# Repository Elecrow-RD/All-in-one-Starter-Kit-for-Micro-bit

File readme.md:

### 1, Product picture

https://www.elecrow.com/all-in-one-starter-kit-for-micro-bit-common-board-design-rich-modules-and-lessons.html

### 2, Product version number

|      | Hardware | Software | Remark |
| ---- | -------- | -------- | ------ |
| 1    | V1.0     | V1.0     | latest |

### 3, product information

- Main Processor IC: micro:bit
- Interface: Type-C Interface
- Size: 195\*170*46(mm)
- Material:PP(Non-toxic)
- Weight: 380g

|                         | [All-in-one Starter Kit for Micro:bit](https://www.elecrow.com/all-in-one-starter-kit-for-micro-bit-common-board-design-rich-modules-and-lessons.html) |
| ----------------------- | ------------------------------------------------------------ |
| Main Processor          | micro:bit                                                    |
| Number of Sensors       | 13 sensors                                                   |
| Sensor Board Design     | Integrated sensor board, no soldering or complex wiring required |
| Programming Environment | Based on micro:bit visual modular programming                |
| Number of Tutorials     | 21 creative tutorials                                        |
| Dimension               | 195x170x46mm                                                 |
| Target Audience         | Students, teachers, hardware enthusiasts                     |
| Application Scenarios   | Ideal for learning micro:bit programming basics              |

### 4,Quick Start

#### Go to the Micro:bit website:https://makecode.microbit.org/

#### Enter the online editor

### 5,Folder structure.

|--3D file： Contains 3D model files (.stp) for the hardware. These files can be used for visualization, enclosure design, or integration into CAD software.

|--Eagle_SCH&PCB: Contains **Eagle CAD** schematic (`.sch`) and PCB layout (`.brd`) files. These are used for circuit design and PCB manufacturing.

|--example: Provides example code and projects to demonstrate how to use the hardware and libraries. These examples help users get started quickly.

### 6,Pin definition

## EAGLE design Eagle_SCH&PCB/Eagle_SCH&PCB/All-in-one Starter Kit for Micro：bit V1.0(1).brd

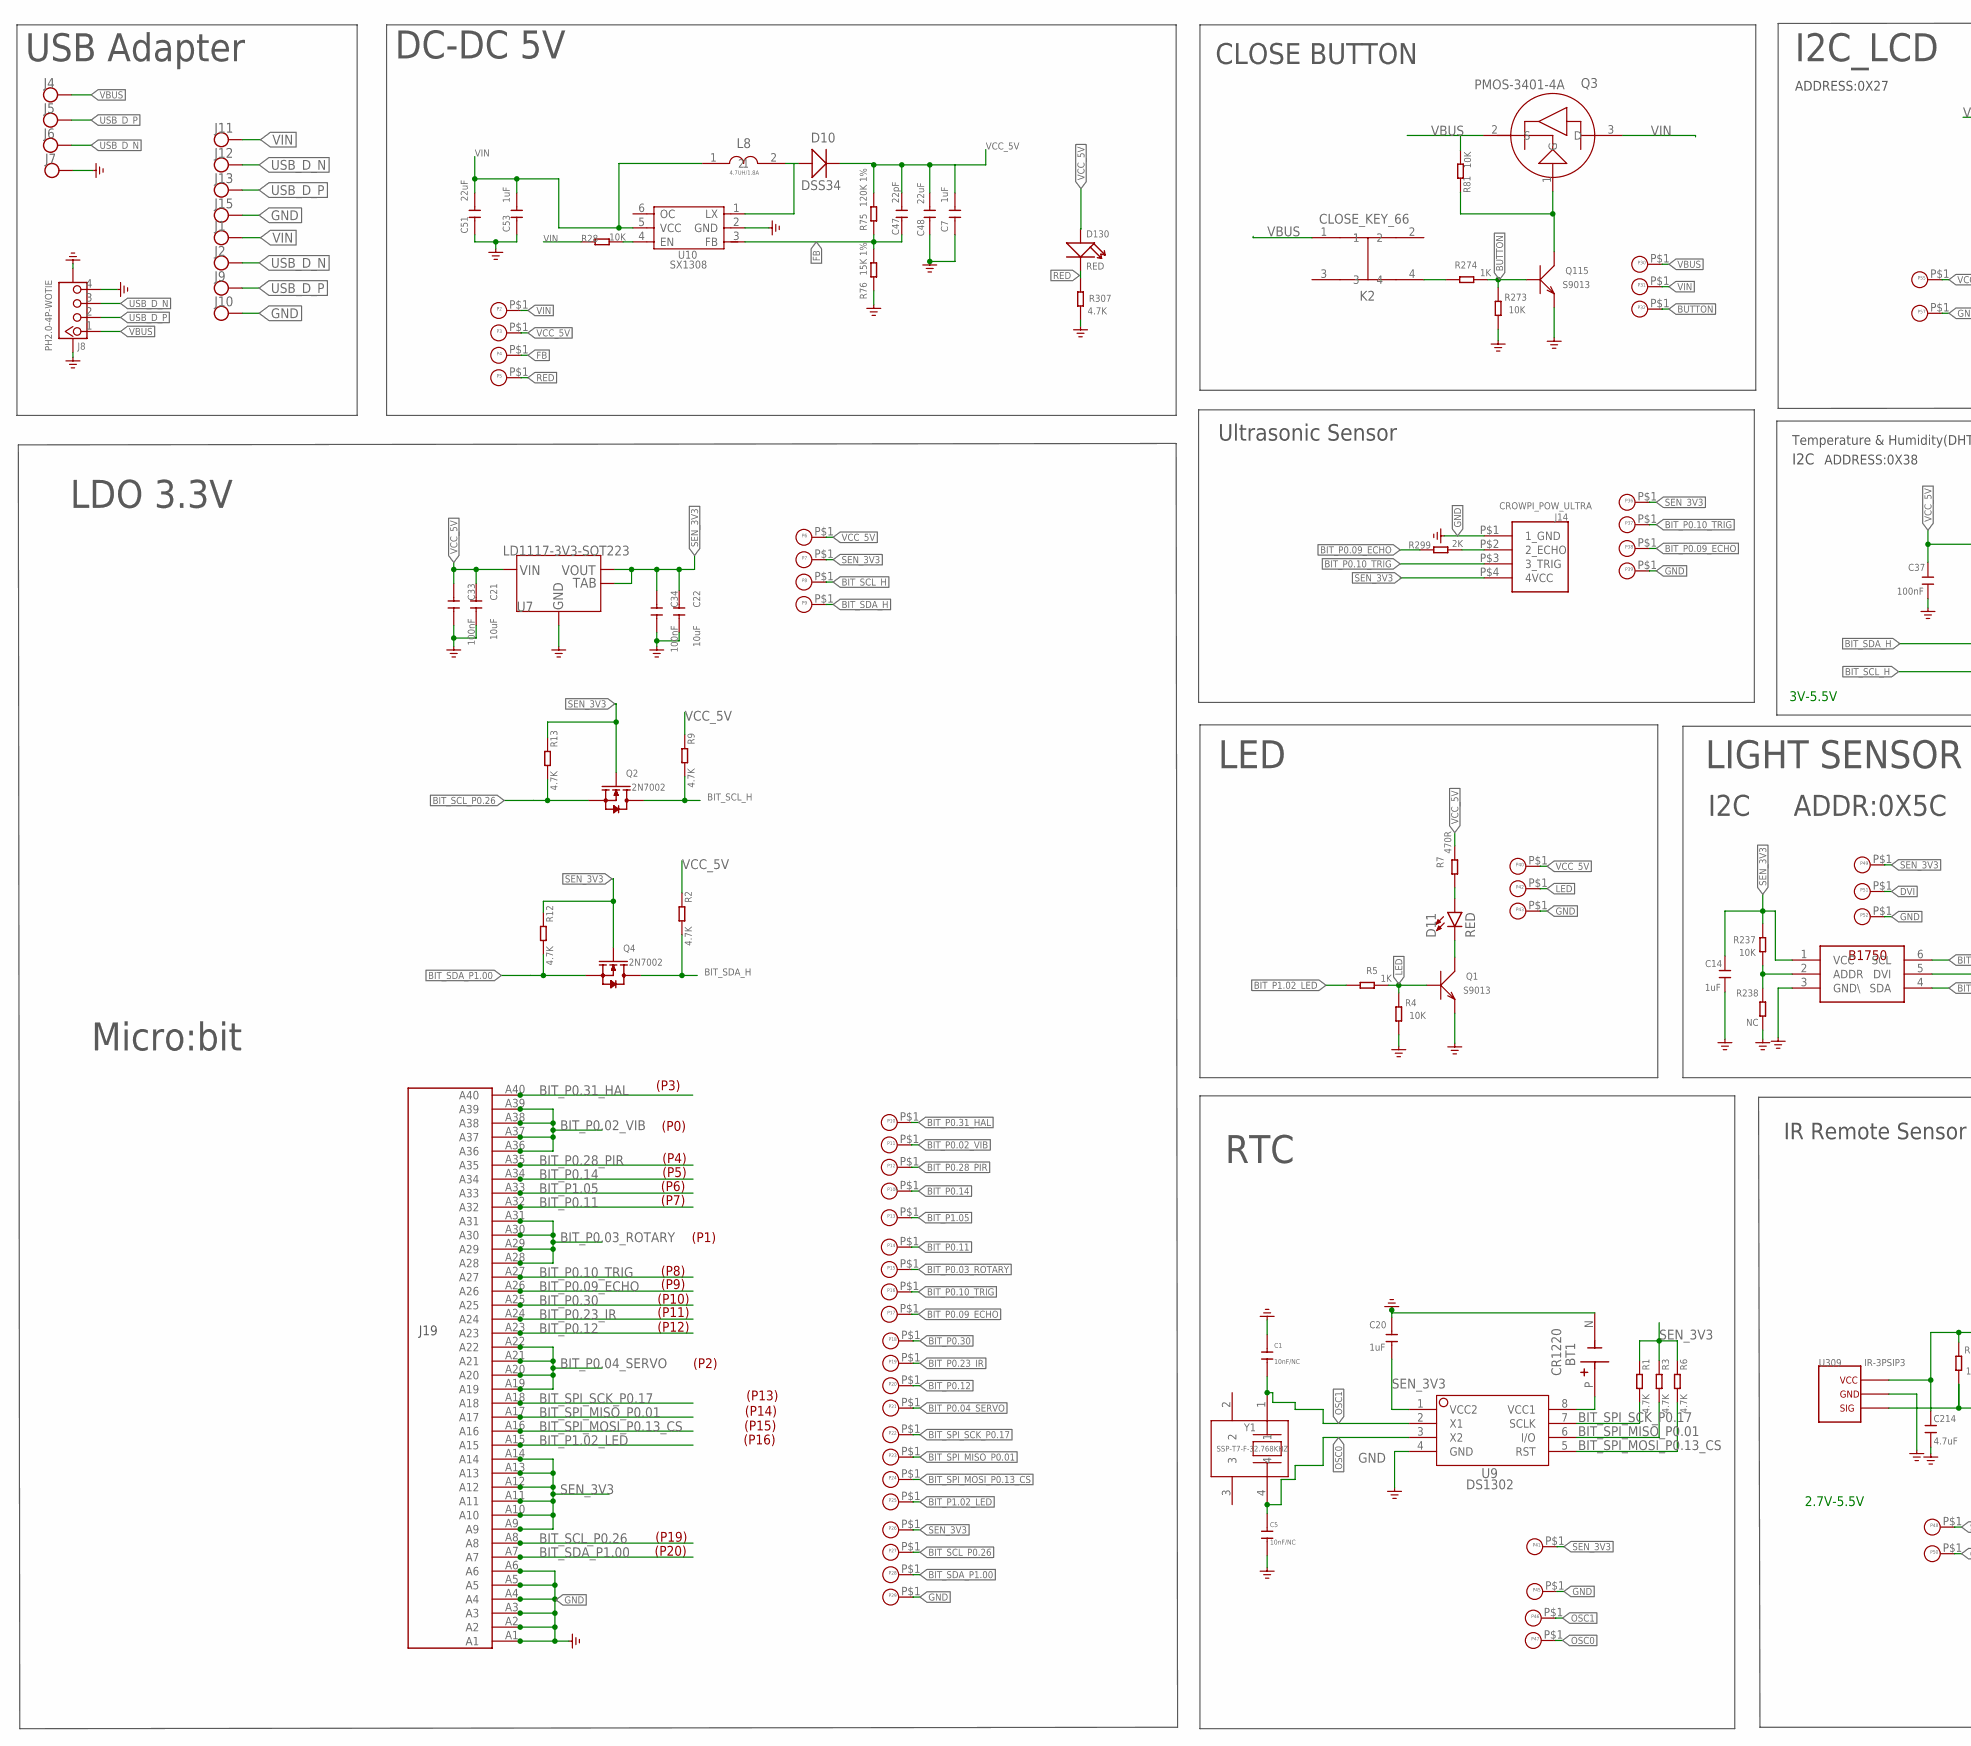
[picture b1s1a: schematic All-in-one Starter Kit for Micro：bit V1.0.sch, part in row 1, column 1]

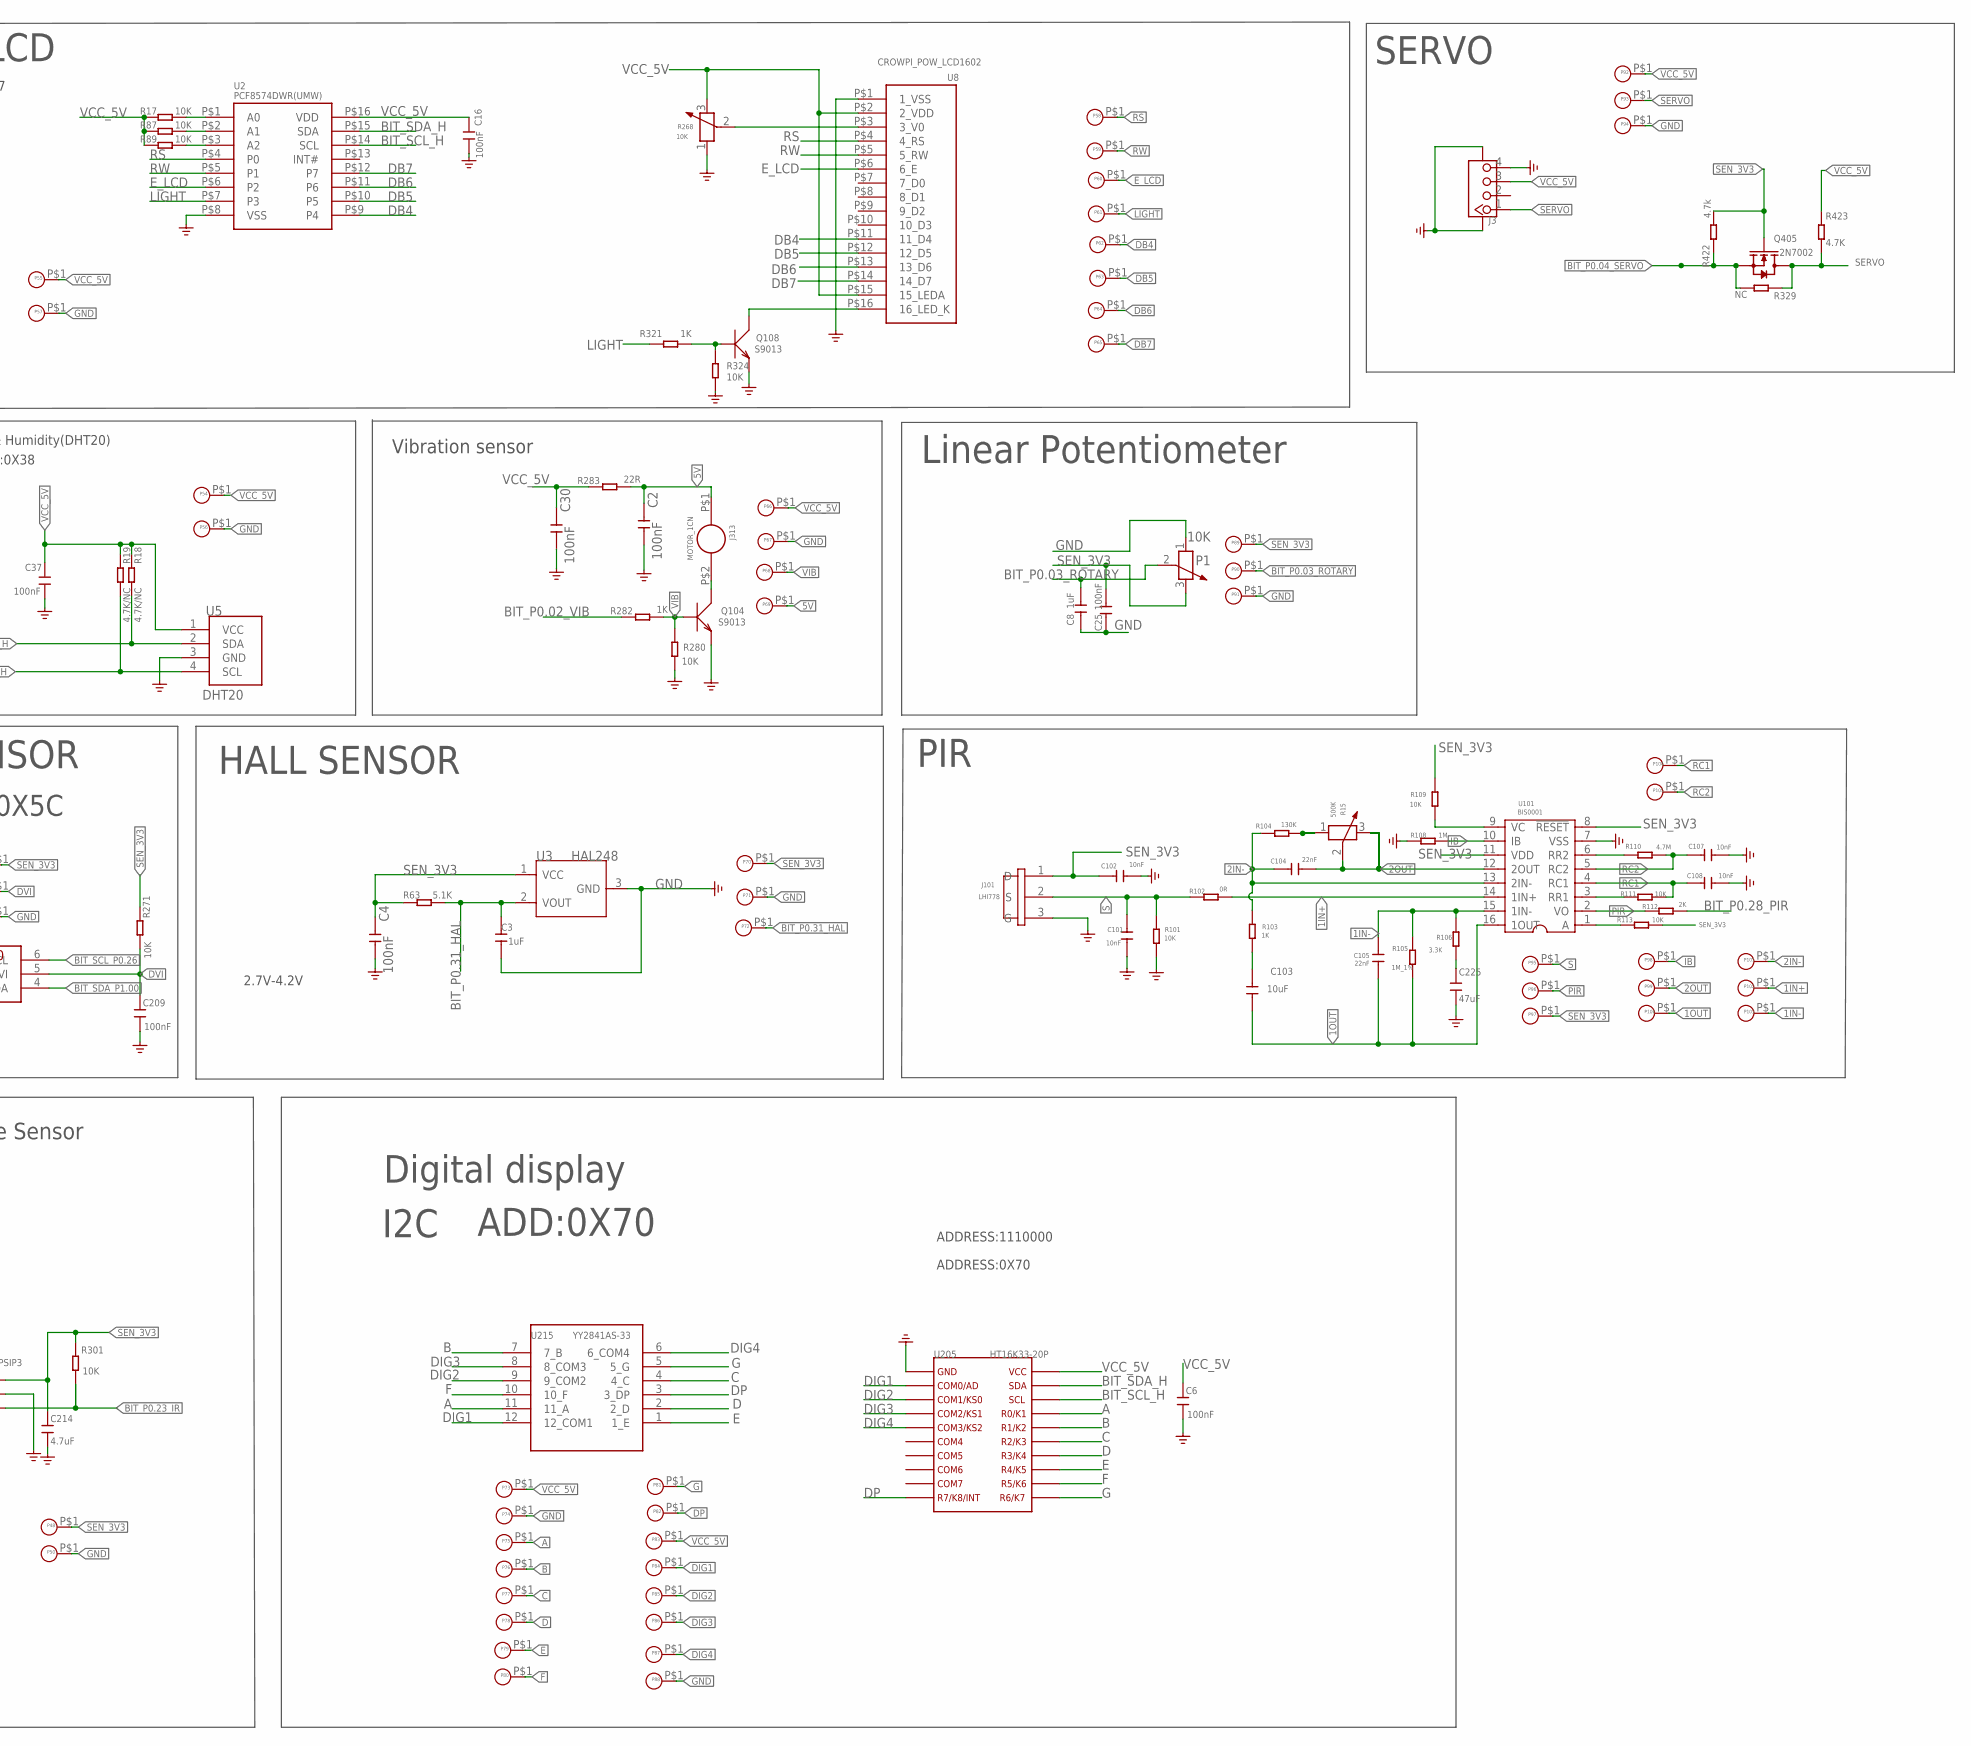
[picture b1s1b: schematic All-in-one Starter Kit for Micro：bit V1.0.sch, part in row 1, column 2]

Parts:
BT1: CR1220
C1, C5: 10nF/NC; C0603
C2, C4, C25, C30, C33, C34: 100nF; C0603
C3, C7, C8, C20, C53: 1uF; C0603
C6, C16, C37, C209: 100nF; 0603
C14: 1uF; 0603
C21, C22: 10uF; C0603
C47: 22pF; C0603
C48, C51: 22uF; C0805
C101, C102, C107, C108: 10nF; C0603
C103: 10uF; 0603
C104, C105: 22nF; C0603
C214: 4.7uF; 0603
C225: 47uF; 0805
D10: DSS34; D_SOD123FL
D11: RED; LED-8MM
D130: RED; LED_0603_SMT
J1, J2, J4, J5, J6, J7, J9, J10, J11, J12, J13, J15: TP-SMDTP-SMD-2X4MM; TP-SMD-2X4MM
J3: A_XBJ_CONNECTOR_TWIG-4P-2.0-SMD-FEMALE-REINFORCE9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; A_XBJ_CONNECTOR_4P-SMD-2.0-90D
J8: PH2.0-4P-WOTIE; PH2.0-4P
J14: CROWPI_POW_ULTRA
J19: MICROBIT_SMD_40P
J101: LHI778; 3P-D8.1MM
J313: MOTOR_1CN; MOTOR_1CM
K2: CLOSE_KEY_66; CLOSE_KEY_6*6
L8: 4.7UH/1.8A; 1008
P1: 10K; 3P-SQUA-45.6X10X5.8H
P2, P3, P4, P5, P6, P7, P8, P9, P10, P11, P12, P13, P14, P15, P16, P17, P18, P19, P20, P21, P22, P23, P24, P25, P26, P27, P28, P29, P30, P31, P32, P36, P37, P38, P39, P40, P41, P42, P43, P45, P46, P47, P48, P49, P50, P51, P52, P54, P55, P56, P57, P58, P59, P60, P61, P62, P63, P64, P65, P66, P67, P68, P69, P70, P71, P72, P73, P74, P75, P76, P77, P78, P79, P80, P81, P82, P83, P84, P85, P86, P87, P88, P89, P90, P91, P92, P93, P94, P95, P96, P97, P98, P99, P100, P101, P102, P103, P104, P105, P106: PADPAD-1.0MM; PAD-1.0MM
Q1, Q104, Q108, Q115: S9013; SOT23@1
Q2, Q4, Q405: 2N7002; SOT23
Q3: PMOS-3401-4A; DFN8_SOT-23
R1, R2, R3, R6, R9, R12, R13, R307, R423: 4.7K; R0603
R4, R17, R87, R89, R101, R109, R111, R113, R237, R271, R273, R280, R301, R324: 10K; R0603
R5, R103, R274, R282, R321: 1K; R0603
R7: 470R; R0603
R15: 500K; 3P-SMD-SQUA-3.6X3.3
R18, R19: 4.7K/NC; R0603
R28: 10K; R0603-SP
R63: 5.1K; R0603
R75: 120K 1%; R0603-SP
R76: 15K 1%; R0603-SP
R81: 10K; DISCRETE_R0603
R102: 0R; R0603
R104: 130K; R0603
R105: 1M_1%; R0603
R106: 3.3K; R0603
R108: 1M; R0603
R110: 4.7M; R0603
R112, R299: 2K; R0603
R238, R329: NC; R0603
R268: 10K; 3P-SMD-SQUA-3.6X3.3
R283: 22R; R0603
R422: 4.7k; R0603
U1: BH1750; BH1750-WSOF-6
U2: PCF8574DWR(UMW); SO-16-300MIL
U3: HAL248; SOT-23W
U5: DHT20; CROWTAIL-DHT20-V1.0-20211013_DHT20
U7: LD1117-3V3-SOT223; SOT223
U8: CROWPI_POW_LCD1602; CROWPI_POW_LCD1206
U9: DS1302; SOP8
U10: SX1308; SOT23-6L
U101: BIS0001; SOP16
U205: HT16K33-20P; HT16K33-SOP20
U215: YY2841AS-33; 4-DIGITAL_DISPLAY
U309: IR-3PSIP3; VS1838B-SIP3
Y1: SSP-T7-F-32.768KHZ; MC-146

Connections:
1IN+: P102.P$1, R102.1, U101.14 (1IN+)
1IN-: C105.2, P103.P$1, R105.2, R106.2, U101.15 (1IN-)
1OUT: C103.2, C105.1, P100.P$1, R105.1, U101.16 (1OUT)
2IN-: C104.1, P101.P$1, R103.2, R104.2, U101.13 (2IN-)
2OUT: C104.2, P99.P$1, R15.2 (3), R15.3 (2), U101.12 (2OUT)
5V: C2.2, J313.P$1, P69.P$1, R283.2
A: P75.P$1, U205.P$17, U215.11 (11_A)
B: P76.P$1, U205.P$16, U215.7 (7_B)
BIT_P0.02_VIB: J19.A36, J19.A37, J19.A38, J19.A39, P11.P$1, R282.1
BIT_P0.03_ROTARY: C8.2, J19.A28, J19.A29, J19.A30, J19.A31, P1.2 (3), P15.P$1, P90.P$1
BIT_P0.04_SERVO: J19.A19, J19.A20, J19.A21, J19.A22, P21.P$1, Q405.2 (S), R329.2, R422.1
BIT_P0.09_ECHO: J19.A26, P17.P$1, P38.P$1, R299.2
BIT_P0.10_TRIG: J14.P$3 (3_TRIG), J19.A27, P16.P$1, P37.P$1
BIT_P0.11: J19.A32, P14.P$1
BIT_P0.12: J19.A23, P20.P$1
BIT_P0.14: J19.A34, P106.P$1
BIT_P0.23_IR: J19.A24, P19.P$1, R301.2, U309.3
BIT_P0.28_PIR: J19.A35, P12.P$1, R112.1
BIT_P0.30: J19.A25, P18.P$1
BIT_P0.31_HAL: C3.1, J19.A40, P10.P$1, P72.P$1, R63.1, U3.2 (VOUT)
BIT_P1.02_LED: J19.A15, P25.P$1, R5.2
BIT_P1.05: J19.A33, P13.P$1
BIT_SCL_H: P8.P$1, Q2.3 (D), R9.2, R19.2, U2.P$14 (SCL), U5.4 (SCL), U205.P$18
BIT_SCL_P0.26: J19.A8, P27.P$1, Q2.2 (S), R13.2, U1.6 (SCL)
BIT_SDA_H: P9.P$1, Q4.3 (D), R2.2, R18.2, U2.P$15 (SDA), U5.2 (SDA), U205.P$19
BIT_SDA_P1.00: J19.A7, P28.P$1, Q4.2 (S), R12.2, U1.4 (SDA)
BIT_SPI_MISO_P0.01: J19.A17, P23.P$1, R3.2, U9.6 (I/O)
BIT_SPI_MOSI_P0.13_CS: J19.A16, P24.P$1, R6.2, U9.5 (RST)
BIT_SPI_SCK_P0.17: J19.A18, P22.P$1, R1.2, U9.7 (SCLK)
BUTTON: P32.P$1, Q115.1 (B), R273.2, R274.1
C: P77.P$1, U205.P$15, U215.4 (4_C)
D: P78.P$1, U205.P$14, U215.2 (2_D)
DB4: P62.P$1, U2.P$9 (P4), U8.P$11 (11_D4)
DB5: P63.P$1, U2.P$10 (P5), U8.P$12 (12_D5)
DB6: P64.P$1, U2.P$11 (P6), U8.P$13 (13_D6)
DB7: P65.P$1, U2.P$12 (P7), U8.P$14 (14_D7)
DIG1: P84.P$1, U205.P$2, U215.12 (12_COM1)
DIG2: P85.P$1, U205.P$3, U215.9 (9_COM2)
DIG3: P86.P$1, U205.P$4, U215.8 (8_COM3)
DIG4: P87.P$1, U205.P$5, U215.6 (6_COM4)
DP: P82.P$1, U205.P$10, U215.3 (3_DP)
DVI: C209.2, P51.P$1, R271.2, U1.5 (DVI)
E: P79.P$1, U205.P$13, U215.1 (1_E)
E_LCD: P60.P$1, U2.P$6 (P2), U8.P$6 (6_E)
F: P80.P$1, U205.P$12, U215.10 (10_F)
FB: C47.2, P4.P$1, R75.1, R76.2, U10.3 (FB)
G: P81.P$1, U205.P$11, U215.5 (5_G)
GND: BT1.N (-), C1.2, C2.1, C3.2, C4.1, C5.1, C6.1, C7.1, C8.1, C14.1, C16.1, C20.2, C21.2, C22.2, C25.1, C30.1, C33.2, C34.2, C37.1, C48.1, C51.1, C53.1, C101.1, C102.1, C107.2, C108.2, C209.1, C214.1, C225.1, J3.4, J3.SS1, J3.SS2, J7.1, J8.4, J8.5 (SS1), J8.6 (SS2), J10.1, J14.P$1 (1_GND), J15.1, J19.A1, J19.A2, J19.A3, J19.A4, J19.A5, J19.A6, J101.3 (G), P1.1, P29.P$1, P39.P$1, P43.P$1, P45.P$1, P50.P$1, P52.P$1, P56.P$1, P57.P$1, P67.P$1, P71.P$1, P74.P$1, P88.P$1, P91.P$1, P94.P$1, Q1.2 (E), Q104.2 (E), Q108.2 (E), Q115.2 (E), R4.1, R76.1, R101.1, R108.1, R238.1, R268.1, R273.1, R280.1, R307.2, R324.2, U1.3 (GND\), U2.P$8 (VSS), U3.3 (GND), U5.3 (GND), U7.1 (GND), U8.P$1 (1_VSS), U9.4 (GND), U10.2 (GND), U101.7 (VSS), U205.P$1, U309.2
IB: P98.P$1, R108.2, U101.10 (IB)
LED: P42.P$1, Q1.1 (B), R4.2, R5.1
LIGHT: P61.P$1, R321.2, U2.P$7 (P3)
unnamed: R111.1, U101.3 (RR1)
unnamed: Q108.1 (B), R321.1, R324.1
unnamed: C225.2, R106.1
unnamed: D10.+, L8.2, U10.1 (LX)
unnamed: Q3.1 (G), Q115.3 (C), R81.1
unnamed: R28.2, U10.4 (EN)
unnamed: R268.2 (3), U8.P$3 (3_V0)
unnamed: K2.4, R274.2
unnamed: BT1.P (+), U9.8 (VCC1)
unnamed: R17.2, U2.P$1 (A0)
unnamed: R87.2, U2.P$2 (A1)
unnamed: R89.2, U2.P$3 (A2)
unnamed: D11.2 (C), Q1.3 (C)
unnamed: D11.1 (A), R7.2
unnamed: Q108.3 (C), U8.P$16 (16_LED_K)
unnamed: R110.2, U101.6 (RR2)
unnamed: R109.2, U101.9 (VC)
unnamed: C103.1, R103.1
unnamed: R113.2, U101.1 (A)
unnamed: R15.1, R104.1
unnamed: J313.P$2, Q104.3 (C)
unnamed: R237.1, R238.2, U1.2 (ADDR)
unnamed: J14.P$2 (2_ECHO), R299.1
OSC0: C5.2, P47.P$1, U9.3 (X2), Y1.4
OSC1: C1.1, P46.P$1, U9.2 (X1), Y1.1
PIR: P96.P$1, R112.2, U101.2 (VO)
RC1: C108.1, P104.P$1, R111.2, U101.4 (RC1)
RC2: C107.1, P105.P$1, R110.1, U101.5 (RC2)
RED: D130.2 (2_K), P5.P$1, R307.1
RS: P58.P$1, U2.P$4 (P0), U8.P$4 (4_RS)
RW: P59.P$1, U2.P$5 (P1), U8.P$5 (5_RW)
S: C101.2, J101.2 (S), P95.P$1, R101.2, R102.2
SEN_3V3: C4.2, C14.2, C20.1, C22.1, C25.2, C34.1, C102.2, C214.2, J14.P$4 (4VCC), J19.A9, J19.A10, J19.A11, J19.A12, J19.A13, J19.A14, J101.1 (D), P1.3 (2), P7.P$1, P26.P$1, P36.P$1, P41.P$1, P48.P$1, P49.P$1, P70.P$1, P89.P$1, P97.P$1, Q2.1 (G), Q4.1 (G), Q405.1 (G), R1.1, R3.1, R6.1, R12.1, R13.1, R63.2, R109.1, R113.1, R237.2, R271.1, R301.1, R422.2, U1.1 (VCC), U3.1 (VCC), U7.2 (VOUT), U7.4 (TAB), U9.1 (VCC2), U101.8 (!RESET), U101.11 (VDD), U309.1
SERVO: J3.1, P93.P$1, Q405.3 (D), R329.1, R423.2
USB_D_N: J2.1, J6.1, J8.3, J12.1
USB_D_P: J5.1, J8.2, J9.1, J13.1
VBUS: J4.1, J8.1, K2.1, P30.P$1, Q3.2 (S), R81.2
VCC_5V: C6.2, C7.2, C16.2, C21.1, C30.2, C33.1, C37.2, C47.1, C48.2, D10.-, D130.1 (1_A), J3.3, P3.P$1, P6.P$1, P40.P$1, P54.P$1, P55.P$1, P66.P$1, P73.P$1, P83.P$1, P92.P$1, R2.1, R7.1, R9.1, R17.1, R18.1, R19.1, R75.2, R87.1, R89.1, R268.3 (2), R283.1, R423.1, U2.P$16 (VDD), U5.1 (VCC), U7.3 (VIN), U8.P$2 (2_VDD), U8.P$15 (15_LEDA), U205.P$20
VIB: P68.P$1, Q104.1 (B), R280.2, R282.2
VIN: C51.2, C53.2, J1.1, J11.1, L8.1, P2.P$1, P31.P$1, Q3.3 (D), R28.1, U10.5 (VCC)

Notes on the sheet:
I2C_LCD
LIGHT SENSOR
SERVO
Ultrasonic Sensor
IR Remote Sensor
I2C
Temperature & Humidity(DHT20)
PIR
CLOSE BUTTON
2.7V-5.5V
3V-5.5V
ADDRESS:0X38
ADDRESS:0X27
LED
Linear Potentiometer
DC-DC 5V
USB Adapter
ADDR:0X5C
Micro:bit
(P20)
(P19)
(P16)
(P15)
(P14)
(P13)
(P2)
(P8)
(P9)
(P10)
(P11)
(P12)
(P1)
(P4)
(P5)
(P6)
(P7)
(P0)
(P3)
LDO 3.3V
Vibration sensor

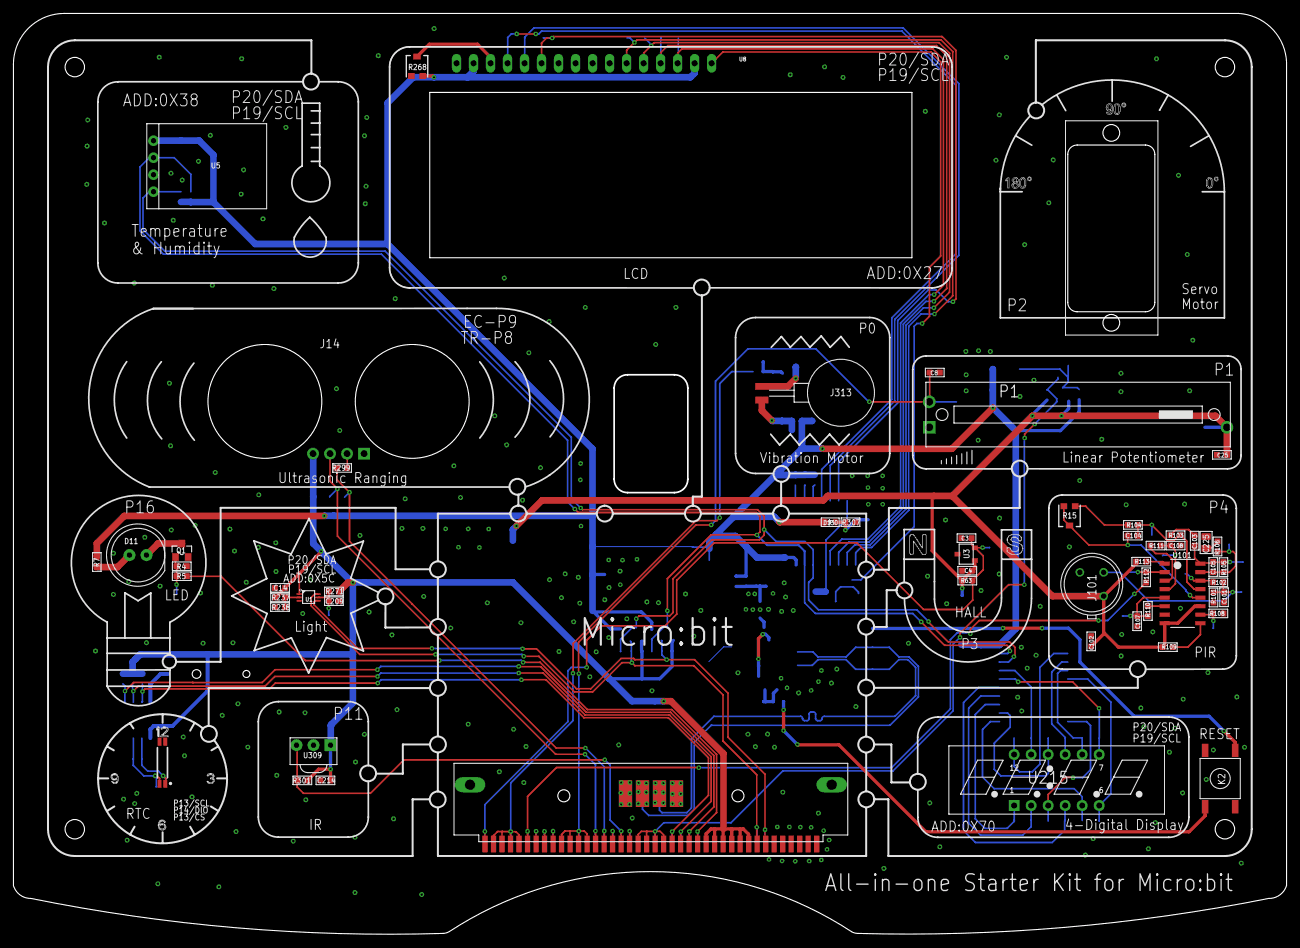
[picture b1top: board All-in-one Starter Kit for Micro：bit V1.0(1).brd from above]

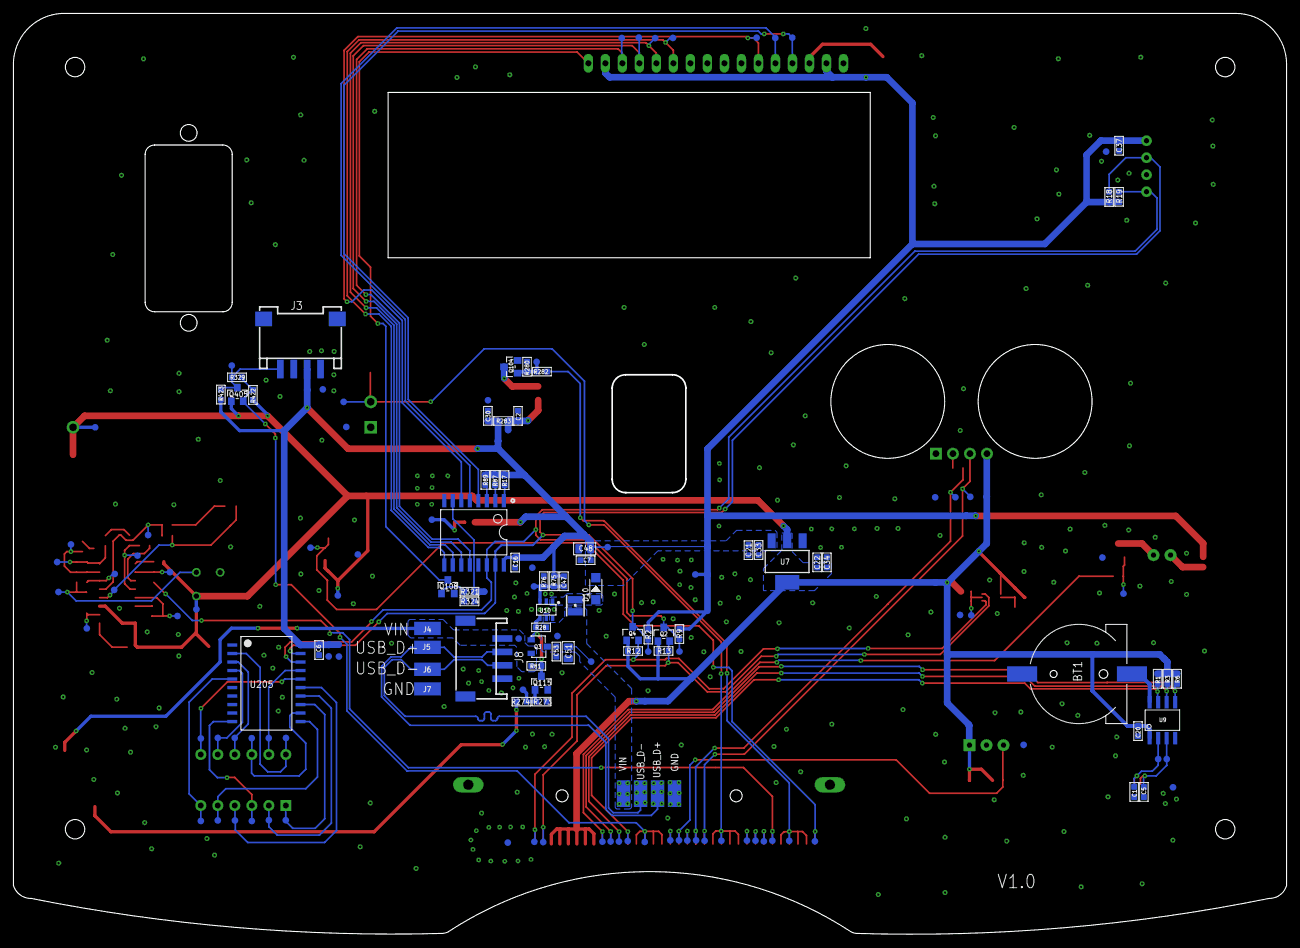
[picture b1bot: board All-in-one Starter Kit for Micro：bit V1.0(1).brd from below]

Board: 2 copper layers, 190.1 x 137.5 mm, 228 parts (168 on the bottom side), 91 nets.
